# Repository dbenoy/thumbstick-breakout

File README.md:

# "PS5 Hall Effect" Compatible Thumbstick Breakout Board
This breakout board is designed to be a drop-in replacement for the Sparkfun BOB-09110 but using hall effect thumbsticks instead of low quality "PS2 style" sticks.

These thumbstick components are widely available on Ali Express as replacement thumbsticks for game controllers. Unlike a traditional potentiometer based joystick, these sticks only operate with a specific polarity, so ensure you select one meant specifically for the PS5 to match the design of this board.

PCBWay order link:<br/>
https://www.pcbway.com/project/shareproject/_PS5_Hall_Effect_Thumbstick_Breakout_Board_abc13f47.html<br/>
(10 for $5 at time of writing. I get a small commission.)

## Datasheet
I couldn't find a datasheet for these stick components, but the datasheet for [this alternative](https://mm.digikey.com/Volume0/opasdata/d220001/medias/docus/2608/THB001P%20drawing.pdf) stick seemed to have measurement information the exact same footprint, so it was used in the creation of this board.

## License
Copyright (c) Daniel Benoy

Distributed under the terms of the [Creative Commons ShareAlike 4.0 International](https://creativecommons.org/licenses/by-sa/4.0/) license.

THESE FILES ARE PROVIDED BY THE COPYRIGHT HOLDERS AND CONTRIBUTORS “AS IS” AND ANY EXPRESS OR IMPLIED WARRANTIES, INCLUDING, BUT NOT LIMITED TO, THE IMPLIED WARRANTIES OF MERCHANTABILITY AND FITNESS FOR A PARTICULAR PURPOSE ARE DISCLAIMED. IN NO EVENT SHALL THE COPYRIGHT OWNER OR CONTRIBUTORS BE LIABLE FOR ANY DIRECT, INDIRECT, INCIDENTAL, SPECIAL, EXEMPLARY, OR CONSEQUENTIAL DAMAGES (INCLUDING, BUT NOT LIMITED TO, PROCUREMENT OF SUBSTITUTE GOODS OR SERVICES; LOSS OF USE, DATA, OR PROFITS; OR BUSINESS INTERRUPTION) HOWEVER CAUSED AND ON ANY THEORY OF LIABILITY, WHETHER IN CONTRACT, STRICT LIABILITY, OR TORT (INCLUDING NEGLIGENCE OR OTHERWISE) ARISING IN ANY WAY OUT OF THE USE OF THIS SOFTWARE, EVEN IF ADVISED OF THE POSSIBILITY OF SUCH DAMAGE.

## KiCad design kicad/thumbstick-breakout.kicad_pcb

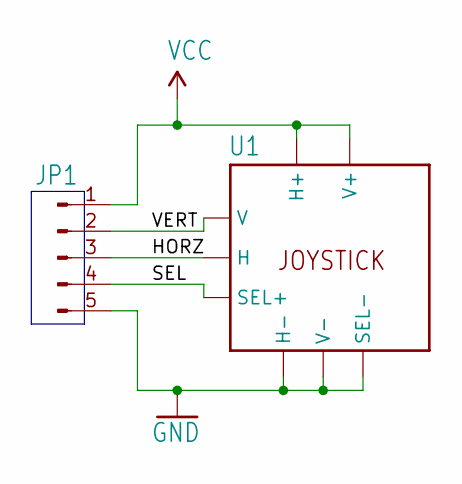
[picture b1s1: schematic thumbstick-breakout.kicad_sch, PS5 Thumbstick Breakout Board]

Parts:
JP1: 1x05
U1: Joystick

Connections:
/HORZ: JP1.3, U1.2 (H)
/SEL: JP1.4, U1.a (SEL+)
/VERT: JP1.2, U1.2' (V)
GND: JP1.5, U1.1 (H-), U1.1' (V-), U1.c (SEL-)
VCC: JP1.1, U1.3 (H+), U1.3' (V+)

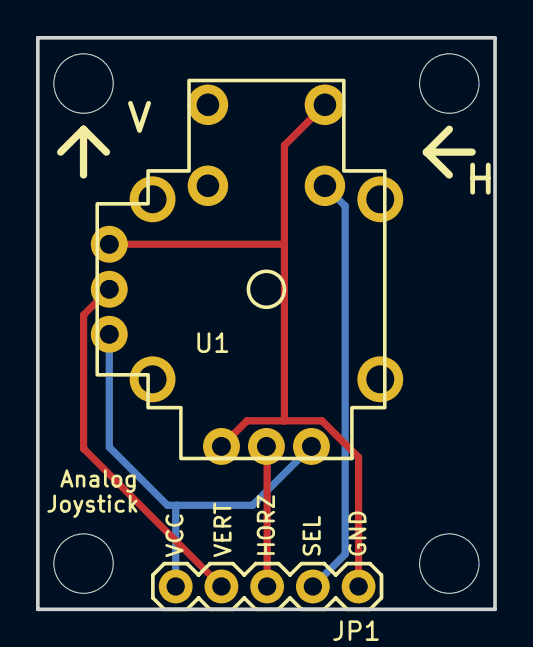
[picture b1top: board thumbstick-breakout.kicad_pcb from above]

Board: 2 copper layers, 25.4 x 31.8 mm, 6 parts (0 on the bottom side), 5 nets.

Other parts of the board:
U$3, U$4, U$5, U$6: Screw Hole

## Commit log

2024-09-13 Moved kicad files to subdirectory
2024-09-13 Initial README update
2024-09-13 Tweaked legal disclaimer
2024-09-13 Added datasheet information
2024-09-13 Fixed typo
2024-09-13 Added PCBWay link
2024-09-13 Cleaned up wording

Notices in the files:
kicad/thumbstick-breakout.kicad_pcb:
This hardware is licensed under Creative Commons ShareAlike 4.0 International
CC BY SA 4.0
